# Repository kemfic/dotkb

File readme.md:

dotkb
---

keyboards, nothing too special. the **micro** is the only one i made so far

the micro
---

features
---
 - MEAT CHECK

LICENSE
---
MIT licensed. don't sue me

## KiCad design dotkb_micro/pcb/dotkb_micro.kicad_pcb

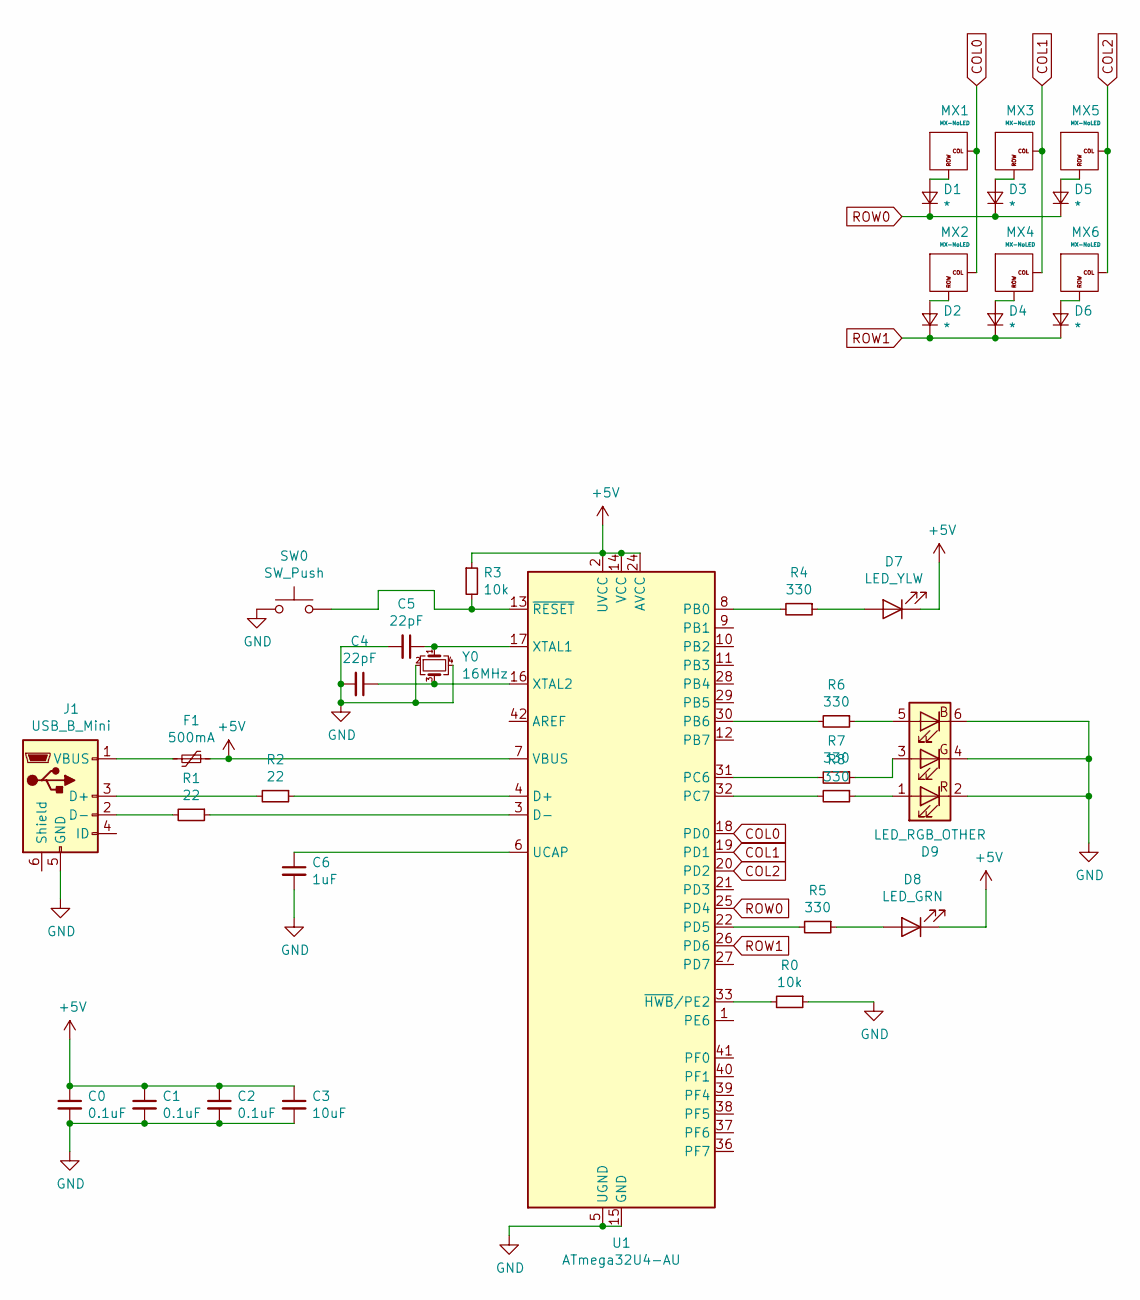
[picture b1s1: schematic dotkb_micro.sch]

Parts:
C0, C1, C2: 0.1uF; C_0805_2012Metric
C3: 10uF; C_0805_2012Metric
C4, C5: 22pF; C_0603_1608Metric_Pad1.05x0.95mm_HandSolder
C6: 1uF; C_0603_1608Metric_Pad1.05x0.95mm_HandSolder; Tolerance +/- 10%
D1, D2, D3, D4, D5, D6: *; D_SOD-123
D7: LED_YLW; LED_0805_2012Metric_Pad1.15x1.40mm_HandSolder
D8: LED_GRN; LED_0805_2012Metric_Pad1.15x1.40mm_HandSolder
D9: LED_RGB_OTHER; LED_RGB_5050-6-135
F1: 500mA; Fuse_1206_3216Metric
J1: USB_B_Mini; USB_Micro-B_Molex_47346-0001
MX1, MX2, MX3, MX4, MX5, MX6: MX-NoLED; SW_Cherry_MX_1.00u_PCB
R0, R3: 10k; R_0805_2012Metric
R1, R2: 22; R_0805_2012Metric
R4, R5, R6, R7, R8: 330; R_0805_2012Metric
SW0: SW_Push; SW_TH_Tactile_Omron_B3F-10xx
U1: ATmega32U4-AU; TQFP-44_10x10mm_P0.8mm
Y0: 16MHz; Crystal_SMD_3225-4Pin_3.2x2.5mm

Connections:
+5V: C0.1, C1.1, C2.1, C3.1, D7.1 (K), D8.1 (K), F1.1, R3.1, U1.2 (UVCC), U1.7 (VBUS), U1.14 (VCC), U1.24 (AVCC), U1.34 (VCC), U1.44 (AVCC)
COL0: MX1.1 (COL), MX2.1 (COL), U1.18 (PD0)
COL1: MX3.1 (COL), MX4.1 (COL), U1.19 (PD1)
COL2: MX5.1 (COL), MX6.1 (COL), U1.20 (PD2)
GND: C0.2, C1.2, C2.2, C3.2, C4.2, C5.2, C6.2, D9.2 (RK), D9.4 (GK), D9.6 (BK), J1.5 (GND), R0.1, SW0.1, U1.5 (UGND), U1.15 (GND), U1.23 (GND), U1.35 (GND), U1.43 (GND), Y0.2, Y0.4
unnamed: C4.1, U1.16 (XTAL2), Y0.3
unnamed: C5.1, U1.17 (XTAL1), Y0.1
unnamed: C6.1, U1.6 (UCAP)
unnamed: D1.2 (A), MX1.2 (ROW)
unnamed: D2.2 (A), MX2.2 (ROW)
unnamed: D3.2 (A), MX3.2 (ROW)
unnamed: D4.2 (A), MX4.2 (ROW)
unnamed: D5.2 (A), MX5.2 (ROW)
unnamed: D6.2 (A), MX6.2 (ROW)
unnamed: D7.2 (A), R4.1
unnamed: D8.2 (A), R5.1
unnamed: D9.1 (RA), R8.1
unnamed: D9.3 (GA), R7.1
unnamed: D9.5 (BA), R6.1
unnamed: F1.2, J1.1 (VBUS)
unnamed: J1.2 (D-), R1.2
unnamed: J1.3 (D+), R2.2
unnamed: R0.2, U1.33 (~HWB~/PE2)
unnamed: R1.1, U1.3 (D-)
unnamed: R2.1, U1.4 (D+)
unnamed: R3.2, SW0.2, U1.13 (~RESET)
unnamed: R4.2, U1.8 (PB0)
unnamed: R5.2, U1.22 (PD5)
unnamed: R6.2, U1.30 (PB6)
unnamed: R7.2, U1.31 (PC6)
unnamed: R8.2, U1.32 (PC7)
ROW0: D1.1 (K), D3.1 (K), D5.1 (K), U1.25 (PD4)
ROW1: D2.1 (K), D4.1 (K), D6.1 (K), U1.26 (PD6)

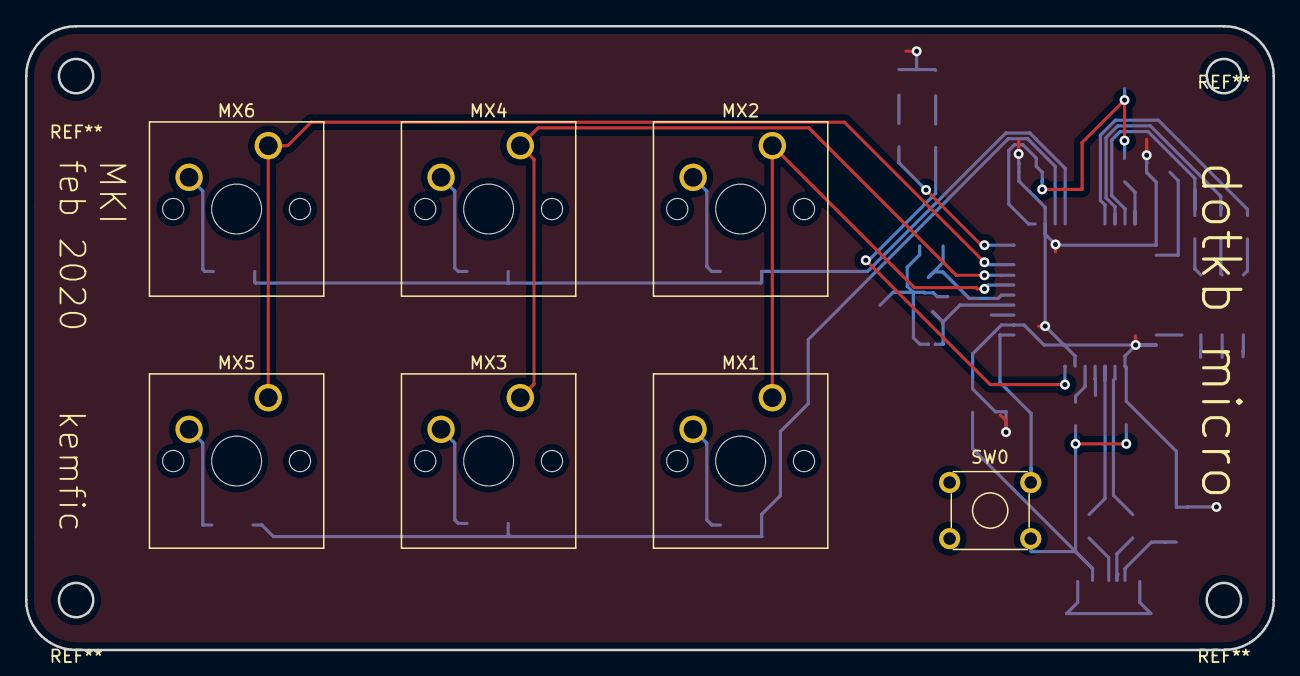
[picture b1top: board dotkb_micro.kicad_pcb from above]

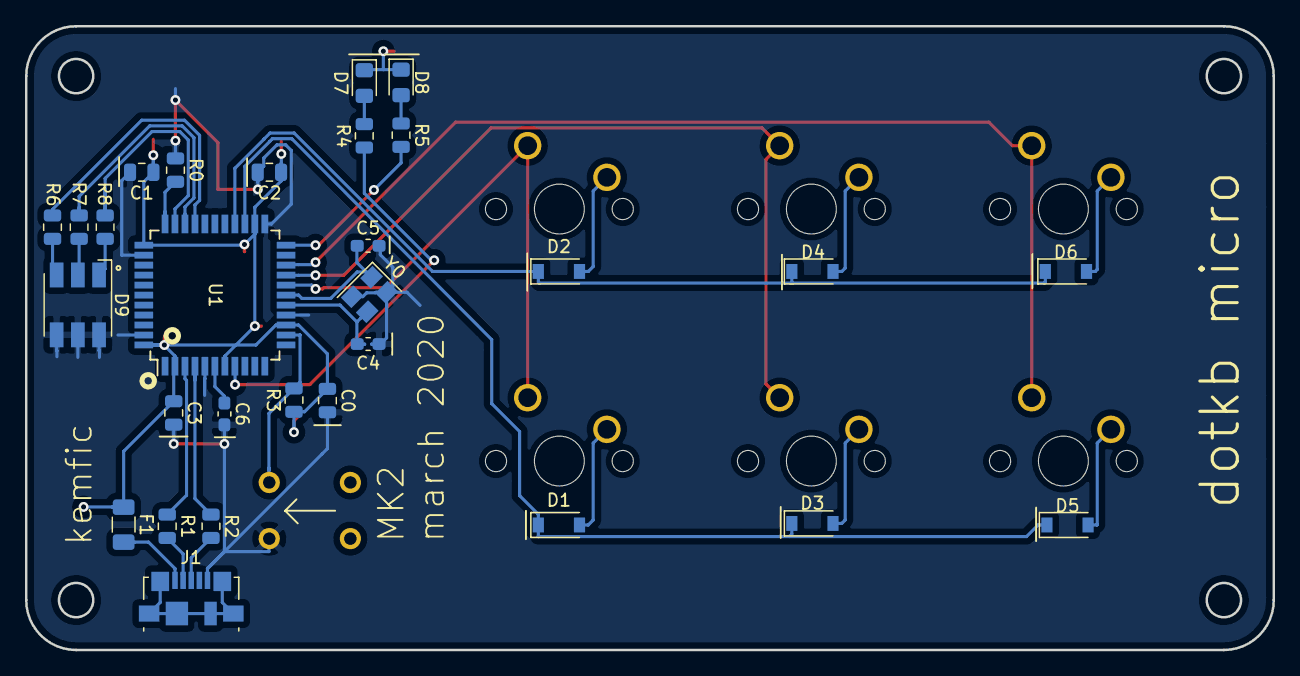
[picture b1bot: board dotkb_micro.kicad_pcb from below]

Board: 2 copper layers, 100.0 x 50.0 mm, 36 parts (29 on the bottom side), 33 nets.

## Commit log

2019-09-28 initial commit ?
2019-10-11 updated layout to 65%
2020-02-24 [micro] added schematic
2020-02-24 added micro BOM
2020-03-15 [dotkb micro] added MK2 and code
